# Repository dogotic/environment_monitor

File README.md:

# EnvMonitor

ESP32-S3 environment monitor with a 2.8" TFT display showing temperature, humidity, clock and date. WiFi credentials are provisioned over BLE from an Android app — no captive portal, no hardcoded SSID.

```
fw/                        # Arduino firmware (.ino)
app/mobile_app/            # Qt/QML Android app (BLE provisioner)
app/build_android.sh       # CLI build + sign script
```

---

## Hardware

| Component | Details |
|-----------|---------|
| MCU | ESP32-S3 Supermini |
| Display | ILI9341 2.8" TFT (320×240, SPI) |
| Sensor | SHT41 temp/humidity (I2C) |

### Wiring

| Signal | GPIO |
|--------|------|
| TFT CS | 10 |
| TFT DC | 9 |
| TFT RST | 8 |
| TFT MOSI | 11 |
| TFT SCK | 13 |
| TFT MISO | 12 |
| I2C SDA (SHT41) | 5 |
| I2C SCL (SHT41) | 6 |

---

## Firmware (`fw/`)

Single `.ino` file, no build system beyond Arduino.

### Libraries

Install via **Arduino Library Manager** or `arduino-cli lib install "<name>"`:

- `Adafruit GFX Library`
- `Adafruit ILI9341`
- `Adafruit SHT4x Library`
- `NimBLE-Arduino`

Board core: **esp32:esp32** (Espressif ESP32 Arduino core).

### Build with arduino-cli

```bash
# Compile
arduino-cli compile --fqbn esp32:esp32:esp32s3 fw/environment_monitor/environment_monitor.ino

# Upload (replace /dev/ttyUSB0 with your port)
arduino-cli upload --fqbn esp32:esp32:esp32s3 -p /dev/ttyUSB0 fw/environment_monitor/environment_monitor.ino

# Serial monitor
arduino-cli monitor -p /dev/ttyUSB0 -c baudrate=115200
```

### Build with Arduino IDE

Open `fw/environment_monitor/environment_monitor.ino`, select board **ESP32S3 Dev Module**, and upload.

### State machine

```
ST_PROVISION  →  ST_CONNECTING  →  ST_ONLINE
     ↑                                  |
     └──────── WiFi drops / BLE write ──┘
```

| State | Behaviour |
|-------|-----------|
| `ST_PROVISION` | No saved credentials — BLE advertising, display shows "WiFi Setup" |
| `ST_CONNECTING` | 15 s WiFi connect attempt, triggered by BLE credential write |
| `ST_ONLINE` | WiFi up, NTP synced (CET/CEST), display refreshes at 1 Hz, sensor polled every 5 s |

Display updates are diff-based: only the region that changed (clock, temperature, humidity, comfort bar) is redrawn — no full `fillScreen` on every frame.

### Firmware internals

**`environment_monitor.ino`** — single-file, no classes beyond the two NimBLE callback structs.

| Symbol | Role |
|--------|------|
| `appState` | Current state machine state (`ST_PROVISION / ST_CONNECTING / ST_ONLINE`) |
| `doConnect` | `volatile bool` flag set by the BLE write callback; consumed in `loop()` to trigger a WiFi connect from the main core |
| `tempC / rhPct` | Last sensor reading (`NAN` until first successful read) |
| `charStat` | Pointer to the BLE status characteristic; used by `bleNotify()` to send status strings |
| `sensorOk` | `false` if `sht4.begin()` failed — sensor readings are skipped and `--` is shown on display |

**BLE callbacks**

- `CredCB::onWrite` — parses the JSON payload with a minimal `jsonField()` helper (no JSON library needed), saves SSID/password to NVS, then sets `doConnect = true`
- `SrvCB::onDisconnect` — restarts advertising so the device is discoverable again after a client disconnects

**Display layout (landscape 320×240)**

```
 ┌─────────────────────────────────────┐
 │ °C  [temp 5×]        [humidity 6×] %│  ← row 0–70
 │          ▼ humidity marker           │  ← row 73–109
 │ [DRY ░░░][COMFORT ░░░░░][WET ░░░░░] │  ← comfort bar row 110–136
 ├─────────────────────────────────────┤  ← separator row 143
 │ AM  HH:MM              DD/MM        │  ← clock + date row 148–188
 └─────────────────────────────────────┘
```

Each region tracks its last-drawn value and redraws only on change:
- Temperature: redraws when value changes by ≥ 0.05 °C
- Humidity: redraws when value changes by ≥ 0.05 %
- Comfort bar + triangle marker: redraws when humidity changes by ≥ 0.5 %
- Clock: redraws when the minute changes
- Date: redraws when the day changes

**Comfort bar thresholds**

| Zone | Humidity range | Color |
|------|---------------|-------|
| DRY | 0–30 % | Amber |
| COMFORT | 30–60 % | Green |
| WET | 60–100 % | Blue |

A white triangle marker points to the current humidity value along the bar.

---

## Android app (`app/mobile_app/`)

Qt/QML app that scans for the `EnvMonitor` BLE device and sends WiFi credentials.

### Requirements

- Qt 6.5+ (uses `QBluetoothPermission` and `qt_standard_project_setup`)
- Android NDK + SDK configured in Qt Creator

### Build in Qt Creator

**File → Open Project → `app/mobile_app/CMakeLists.txt`**, then **Run → Android device**.

### Build from command line

```bash
cd app
./build_android.sh
```

The script reads Qt/SDK paths from `$HOME/Qt` and `$HOME/Android/Sdk`. For a release build supply your own keystore:

```bash
KEYSTORE=/path/to/release.keystore \
KS_PASS=yourpassword \
KS_ALIAS=youralias \
./build_android.sh
```

> The script defaults to the Android debug keystore (`~/.android/debug.keystore`, password `android`). Fine for development — use a real keystore for Play Store releases.

---

## BLE provisioning protocol

The Android app and the firmware share these UUIDs and JSON format:

| Role | UUID |
|------|------|
| Service | `12345678-1234-5678-1234-56789abcdef0` |
| Credentials (WRITE) | `12345678-1234-5678-1234-56789abcdef1` |
| Status (READ \| NOTIFY) | `12345678-1234-5678-1234-56789abcdef2` |

**Client → device** (write to credentials characteristic):
```json
{"ssid": "MyNetwork", "pass": "hunter2"}
```

**Device → client** (notification on status characteristic):

| Value | Meaning |
|-------|---------|
| `connecting` | Connect attempt started |
| `ok:<ip>` | Connected — IP address included |
| `fail` | Wrong SSID or password |

Credentials are stored in NVS via `Preferences` and survive reboots.

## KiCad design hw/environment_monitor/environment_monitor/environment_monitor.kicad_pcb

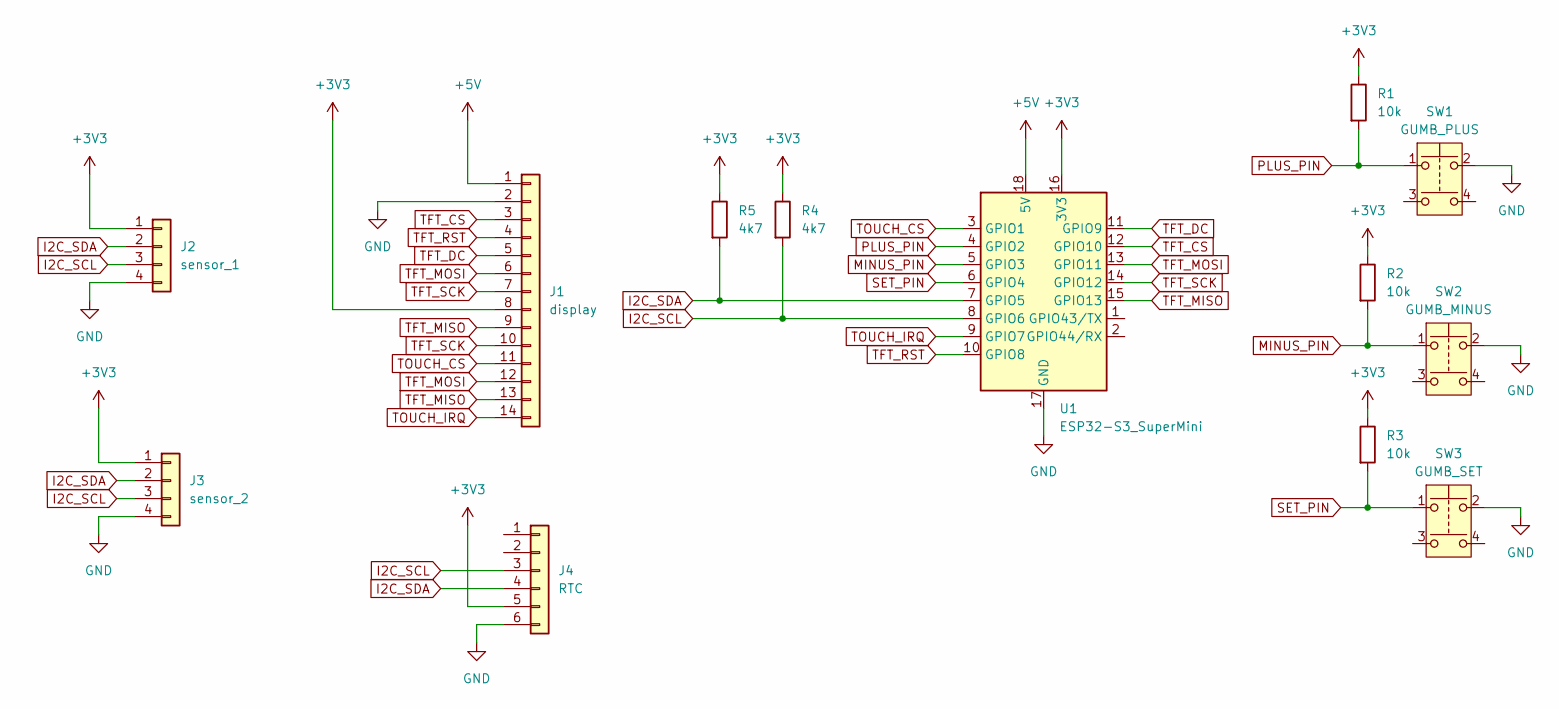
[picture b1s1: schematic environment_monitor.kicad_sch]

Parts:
J1: display; PinSocket_1x14_P2.54mm_Vertical
J2: sensor_1; PhoenixContact_MC_1,5_4-G-3.5_1x04_P3.50mm_Horizontal
J3: sensor_2; PhoenixContact_MC_1,5_4-G-3.5_1x04_P3.50mm_Horizontal
J4: RTC; PinSocket_1x06_P2.54mm_Horizontal
R1, R2, R3: 10k; R_Axial_DIN0309_L9.0mm_D3.2mm_P12.70mm_Horizontal
R4, R5: 4k7; R_Axial_DIN0309_L9.0mm_D3.2mm_P12.70mm_Horizontal
SW1: GUMB_PLUS; SW_PUSH_6mm
SW2: GUMB_MINUS; SW_PUSH_6mm
SW3: GUMB_SET; SW_PUSH_6mm
U1: ESP32-S3_SuperMini; ESP32-S3_SuperMini_THT

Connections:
+3V3: J1.8, J2.1, J3.1, J4.5, R1.1, R2.1, R3.1, R4.1, R5.1, U1.16 (3V3)
+5V: J1.1, U1.18 (5V)
GND: J1.2, J2.4, J3.4, J4.6, SW1.2, SW2.2, SW3.2, U1.17 (GND)
I2C_SCL: J2.3, J3.3, J4.3, R4.2, U1.8 (GPIO6)
I2C_SDA: J2.2, J3.2, J4.4, R5.2, U1.7 (GPIO5)
MINUS_PIN: R2.2, SW2.1, U1.5 (GPIO3)
PLUS_PIN: R1.2, SW1.1, U1.4 (GPIO2)
SET_PIN: R3.2, SW3.1, U1.6 (GPIO4)
TFT_CS: J1.3, U1.12 (GPIO10)
TFT_DC: J1.5, U1.11 (GPIO9)
TFT_MISO: J1.9, J1.13, U1.15 (GPIO13)
TFT_MOSI: J1.6, J1.12, U1.13 (GPIO11)
TFT_RST: J1.4, U1.10 (GPIO8)
TFT_SCK: J1.7, J1.10, U1.14 (GPIO12)
TOUCH_CS: J1.11, U1.3 (GPIO1)
TOUCH_IRQ: J1.14, U1.9 (GPIO7)

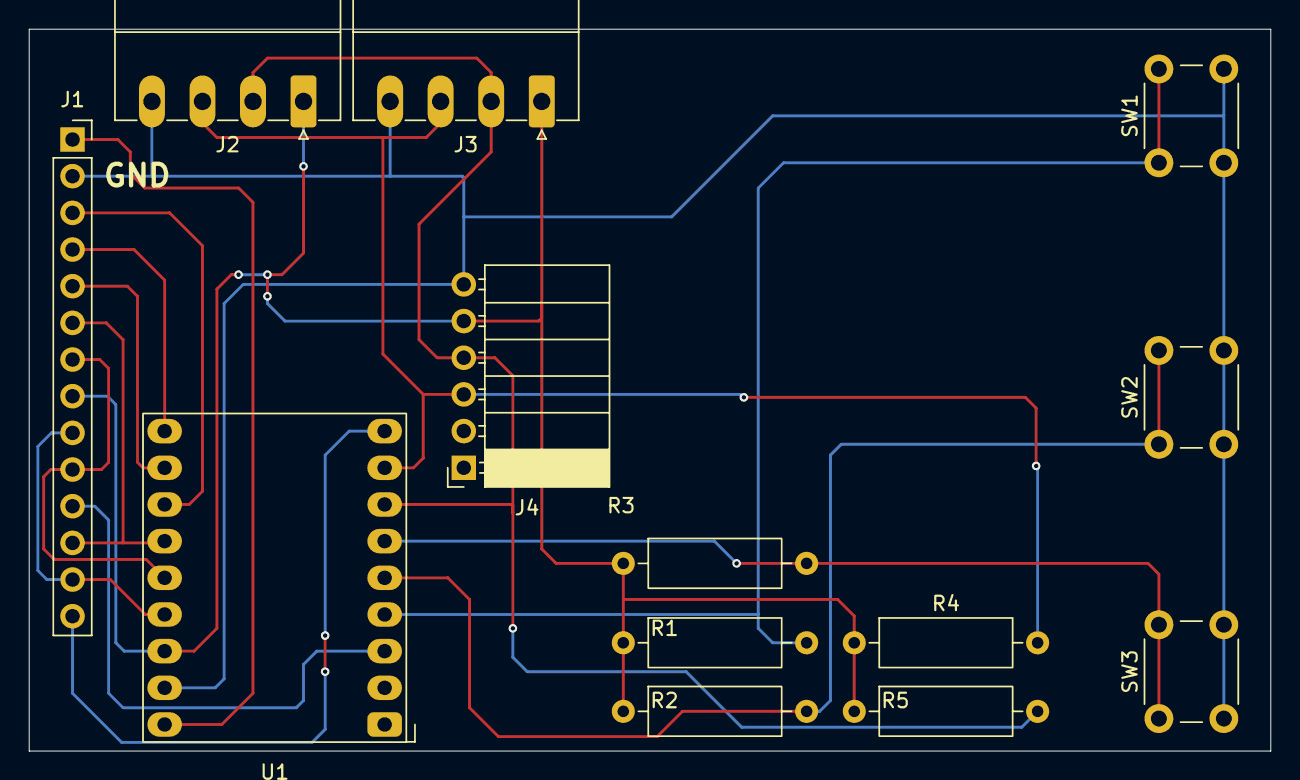
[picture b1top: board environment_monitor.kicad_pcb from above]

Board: 2 copper layers, 86.0 x 50.0 mm, 13 parts (0 on the bottom side), 16 nets.

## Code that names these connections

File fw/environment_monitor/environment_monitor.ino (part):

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// ── Pins ──────────────────────────────────────────────────────────
#define PIN_SDA  5
#define PIN_SCL  6
#define TFT_CS   10
#define TFT_DC    9
#define TFT_MOSI 11
#define TFT_SCK  13
#define TFT_RST   8
#define TFT_MISO 12

// ── Timezone ──────────────────────────────────────────────────────
// RTC i sistemski sat drže UTC; lokalno vrijeme se računa preko TZ.
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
